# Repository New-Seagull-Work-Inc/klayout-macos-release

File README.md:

> **Binary release** — prebuilt `klayout` and `kplace`
> executables for macOS on Apple Silicon (arm64).
> Links against the system libSystem only; no other dependencies.
> Other platforms and distributions: build from the source
> repository when authorized by Seagull Work, Inc.
> **This package contains executables, one example
> KiCad board and the fab library — no source code is
> included or implied.**
> The `klayout` and `kplace` binaries, this README, the
> `LICENSE`, the `example/` board they route and the `fab/`
> folder (the fabs' published capabilities and stackups,
> JSON) are the entire distribution: there is no source tree, no
> Makefile, and nothing here that can be compiled,
> rebuilt, or modified. The example is design input for
> the tool, not program source.
> Nothing to build here: route the included board with
> `./klayout --input-dir example --output-dir out --resize-pcb`.
> Keep both binaries in the same directory: klayout invokes
> kplace for auto-placement and re-invokes itself for parallel
> attempts (install on PATH or run from their directory).
> kicad-cli from KiCad 10, found via PATH or KICAD_CLI,
> enables the DRC acceptance gates, zone-fill verification
> for the pour stitching, and the fab exports (gerbers,
> drill, pick-and-place, IPC-D-356).
> The `fab/` folder is the fab library the impedance model and the
> fab targeting read; it is described below.
> **Trial software, no warranty** — free to evaluate, and
> the layouts it produces are yours to use for anything,
> commercially included. Nothing it outputs is guaranteed
> or has been reviewed by an engineer: a clean DRC report
> is this program grading its own work, not an assurance
> that a board is manufacturable or safe. Verify every
> layout before you build it. Full terms in `LICENSE`.
> The build instructions carried by the source repository are
> omitted from this README: there is nothing here to compile.

# klayout — automatic placement and routing for KiCad boards

**Trial software.** This package is provided for evaluation under the
terms of the `LICENSE` file beside it. Read it before you use the
program; the layouts it produces are yours, the program is not.

## What it does

`klayout` takes a KiCad project — schematic, unrouted board, footprints —
and delivers a placed and routed board:

- **Places** the parts (`kplace`, invoked automatically) the way an
  experienced layout engineer would, from the board alone: every chip
  gets its decoupling and its two-pad satellites in rows along the
  edge that carries their pins; chips cluster into functional blocks
  (a regulator and its parts, a charger and its parts) ordered from
  the input connector; a connector's circuit sits at the connector,
  with the USB pair short and straight from the jack. Boards of four
  copper layers and up are placed on both faces from the first
  trial; two-layer boards start single-sided and go to both faces
  only when no single-sided trial routes every net.
  `--group-labeling` frames and names each block on the silkscreen
  (`Battery charger (U3)`, `Boost converter (U10)`).
- **Routes** every net on the layer count you ask for, through vias,
  with copper pours for the ground and power planes it reserves, and
  power rails at their IPC-2221 ampacity width.
- **Signal integrity built in.** Differential pairs are detected from
  the net names and routed as coupled pairs to their standard's
  impedance and skew budget (USB, PCIe, MIPI CSI/DSI, LVDS, Ethernet).
  DDR interfaces (DDR4, LPDDR4) are detected the same way: each byte
  lane is routed as a bundle on one inner layer with its strobe pair,
  length-matched to the strobe, at the standard's single-ended and
  differential impedance on the fab's real stackup.
- **Judges the signal integrity like a reviewer would.** DDR groups are
  gated on two tiers — the standard's spec (what training absorbs) and
  a shipped-quality target — and their impedance is judged against the
  DRAM's *legal* termination bins (LPDDR4 ODT 40/48/60/80/120/240 Ω) so
  the report names the firmware setting the copper needs. Home layers
  are ranked by the impedance they can actually carry on the fab's
  stackup (a 6-layer board's DDR lands on the outer layers, as the
  reference SoMs do). The **SI sign-off page** (below) adds eye
  diagrams, per-net openings, a timing budget and via-stub analysis.
- **Checks its own work.** Every board goes through KiCad's own DRC
  and ERC (`kicad-cli`); the verdict is `clean` only at zero errors,
  zero warnings, zero unconnected items, zero schematic-parity findings.
- **Tries several placements in parallel** and keeps the one that
  meets every gate, printing a table of the trials so you can see why.
- **Shows you the work as it happens** — the PCB Layout Cinema, a live
  view in your browser (below).
- **Builds to your fab's floors.** `--fab NAME` raises every design
  rule below the house's published minimums for the board's layer
  count, writes its stackup into the board, and judges the input at
  those floors too, so a footprint the house cannot etch is named as
  the input's problem, not the router's.
- **Delivers the fabrication package**: gerbers, drill files and maps,
  IPC-D-356 netlist, a sourced BOM, pick-and-place, fab drawings, a
  board render, the schematic as PDF, a copy of the design and a
  SHA-256 manifest, unless you ask it not to.
- **Keeps the console quiet.** A run prints one status line per
  trial (placing, routing pass, rip-up round, DRC, done) and the
  verdict; everything else goes to `klayout.log`.

## Quick start

```
./klayout --input-dir my-board --output-dir my-board-routed --layers 4
```

- `--input-dir` — a folder holding the KiCad project: the `.kicad_pcb`
  (parts may be unplaced; the design rules come from its `.kicad_pro`),
  the `.kicad_sch`, and the footprint / symbol libraries it uses.
- `--output-dir` — where the routed project is written. It is created.
- `--layers` — copper layers to route on (2, 4, 6, 8, 10, 12 …; `1`
  for a single-sided board with no vias).

Keep `klayout` and `kplace` in the same directory: `klayout` runs
`kplace` for placement and re-runs itself for the parallel attempts.

### What you get

Everything a run produces lives in the output directory:

```
my-board-routed/
  <board>.kicad_pcb            the placed and routed board: opens in KiCad,
                               pours filled, the fab's stackup written in,
                               designators straightened and kept off silk
  <board>.kicad_pro, .kicad_prl, .kicad_sch, fp-lib-table, sym-lib-table,
  <libs>.pretty/, <libs>.kicad_sym
                               the rest of the project, copied beside the
                               board so it opens as a whole; the project's
                               DRC minimums raised to the fab's floors
  <board>-klayout-result.json  the verdict (below)
  klayout.log                  everything the run did: the trial table,
                               placement and routing passes, the impedance,
                               skew and reflection reports, DRC and ERC
  placement-report.txt         boards that were placed: wirelength before
                               and after, the pin pulls, each part's move
                               (beside the board, or in the kept trial's
                               folder when that trial placed it)
  si-report/                   boards built on a fab's stackup: the copper
                               as laid, per net — segments.csv, vias.csv,
                               pads.csv — the reflection data an SI review
                               starts from, and si-report.pdf built on it
                               (reflections per DDR net; per serial lane its
                               eye at the receiver and its impedance along
                               the lane)
  fabrication/                 the manufacturing package (below);
                               --gerber-dir moves it, --no-fab skips it
  .input/                      a read-only copy of the input, judged by the
                               same DRC at the fab's floors, so the verdict
                               can separate the board's own violations from
                               anything the router introduced
  .att0/ … .att7/, .att0.log … the placement trials, each a full project
                               with that trial's board and log (hidden
                               dot-files; `ls -a`)
  <board>.progress.json        the frame the PCB Layout Cinema is drawing
  <board>.progress.jsonl       every frame of that trial, one per line (each
                               holds what changed since the frame before), so
                               the Cinema plays the run back after it ends
```

The fabrication package, in the layout a board house and an assembler
both expect:

```
fabrication/
  gerbers/            <board>-<Layer>.gbr for every copper, mask, silk and
                      paste layer plus the outline, and <board>-job.gbrjob
    drill/            <board>-PTH.drl, <board>-NPTH.drl (Excellon, mm), a
                      PDF drill map per file, drill-report.rpt
  electrical-test/    <board>.d356 — the IPC-D-356 netlist for bare-board test
  assembly/           <board>-bom.csv — one row per reference: Reference,
                      Value, Footprint, Quantity, Manufacturer, MPN,
                      Datasheet, Lifecycle, Supplier, SKU, Product URL,
                      Available, Verified On, Unit Price, DNP
                      <board>-positions.csv — pick-and-place, both sides,
                      mm, populated parts only
                      for a JLCPCB board also <board>-bom-jlcpcb.csv —
                      Comment, Designator, Footprint, LCSC (from each
                      part record; blank where it has none) — and
                      <board>-positions-jlcpcb.csv — Designator, Mid X,
                      Mid Y, Layer, Rotation (rotations as KiCad
                      exports them: check bottom parts in JLCPCB's
                      placement preview)
                      drawings-svg/ — front and back fab drawings
  documentation/      <board>-board-render.png (top view),
                      schematic/<board>.pdf, si-report.pdf (a copy of
                      si-report/si-report.pdf), pdn-impedance.html and
                      .csv (the rail impedance curves, when the board
                      declares rails)
  design/             the board, project, schematic, tables and libraries
                      as sent to manufacture
  manifest.json       every file with its size and SHA-256, the source
                      board's hash, the kicad-cli version, the run's DRC counts
```

The BOM's sourcing columns come from the footprint's own fields
(Manufacturer, MPN, Datasheet) when the schematic carries them, and
otherwise from the parts library (below). The library holds each
part's design record, and the BOM takes from it the manufacturer, the
part number, the datasheet when the record names one, and, where the
record carries them, the distributor, the stock and the lowest-volume
price (a bare number: the record states no currency). Lifecycle, SKU,
product link and verification date are not in a design record and stay
empty. A part with no record keeps its row with those columns empty, so
the BOM always lists every part on the board.

### The PCB Layout Cinema

Every run serves a live view of the routing and opens it in your default
browser (Safari, Chrome and Firefox all work):

```
http://localhost:8765/
```

One panel per placement trial, drawn as it routes — the copper laid
since the last frame in white — with completion bars per signal class
(differential pairs and DDR, other signals, power), the current stage,
the elapsed time, and a scrub bar over the run's frames. **Step frame by
frame** with the ‹ › buttons beside the bar, or click a panel and use
the ← → keys (space returns to live); the counter shows which frame you
are on. Every frame is kept on disk in each trial's
<board>.progress.jsonl, so a reloaded page, or `--watch` on a finished
run or on its archived copy, steps through all of them. The run ends on two frames: what the last pass laid, highlighted
white, then the finished board in its layer colours.
Once a trial is kept the title reads **writing outputs** while the
run writes the board, the fabrication package and the reports -- the
clock runs on -- and **ended** when the run is done.
If the page does not open by itself, open that address (or
`http://127.0.0.1:8765/`) while the run is going. To watch a finished
run again:

```
./klayout --watch my-board-routed
```

`KLAYOUT_NO_BROWSER=1` keeps the browser closed (the server still runs),
`KLAYOUT_DASH_PORT=NNNN` picks another port, `KLAYOUT_NO_DASH=1` turns
the Cinema off.

## Other options

All options are `klayout --help`. The ones you are likely to use:

| option | meaning |
|---|---|
| `--plane NET:LAYER` | pour a copper zone for that net on that layer (`--plane GND:In2.Cu`); repeatable. Without it the tool reserves ground and power layers itself from the layer count. |
| `--stack SPEC` | the stackup by role, outermost first, e.g. `SIG-GND-SIG-GND-PWR:3V3-SIG`; sets `--layers` and the planes at once. |
| `--place-tries N` | placement trials in the first wave (default: as many as the machine has performance and super cores, all at once). A trial that ends without a clean board hands its slot to a new trial with a new placement, until one is clean. The first **clean** trial -- every gate met, and no DRC error, DRC warning or unconnected item added over the input -- stops the others and is kept. Each trial's line in the log names what it left unconnected (`trial 3/6 left unconnected: NET: Pad 2 of C12 -- Track ... at (x, y)`). |
| `--seed N` | base placement seed (default 1) — same command, same board, same result. |
| `--resize-pcb` | after routing, shrink the outline to the smallest DRC-legal rectangle around the design. |
| `--grid`, `--track`, `--clearance`, `--via-size`, `--via-drill`, `--edge-clearance`, `--hole-clearance` (mm) | override the design rules read from the `.kicad_pro`. |
| `--fab NAME` | the board house you will use: its floors become the minimum for every rule and its stackup is written into the board (see the fab library below). |
| `--fab-dir DIR` | where the fab library is (default: `fab/` beside the binaries; `KLAYOUT_FAB_DIR` does the same; `none` runs without it). |
| `--group-labeling` | frame and name the functional blocks on the front silkscreen; off, the blocks pack as tightly as the rows allow and nothing is drawn. |
| `--no-fab` | skip the fabrication package. |
| `--gerber-dir DIR` | write the fabrication package somewhere else. |
| `--split-ps` | split a board larger than a power supply into `<base>-PS` (the mains sheet) and `<base>-MB` (everything else) and route the two separately. |
| `--si-layer-min F` | the share of a DDR lane member's copper that must stay on its home layer (default 0.90); `--si-any-layer` lifts the home-layer rule altogether. |
| `--eight-angles-routing` | 90°/45° turns only, no any-angle shortcuts. Every board is tried this way first; only a board that ends below its gates is retried any-angle, and a DDR board that is complete and DRC-clean stays octilinear. |
| `--arc-wiggles`, `--sine-wiggles` | the shape of length-matching meanders: arc accordions or sinusoids instead of rectangular bumps. |
| `--no-widen` | ignore `power.json`: route power rails at the class width instead of their IPC-2221 ampacity width. |
| `--watch DIR` | serve the PCB Layout Cinema for a finished run. |
| `--version` | print the build revision. |

Environment: `KICAD_CLI=/path/to/kicad-cli` if it is not on your PATH;
`KLAYOUT_OFFLINE=1` to keep the tool from touching the network;
`KLAYOUT_NO_SWEEP=1` to skip the fab sweep (below) when a board ends
below its gates.

## The parts library

The parts library ships beside the executables as `parts/`: the fab library and the parts the
examples use. klayout reads it from there; nothing else is needed.

## The fab library — the `fab/` folder

Four JSON files, one per board house — `jlcpcb.json`, `osh_park.json`,
`advanced_circuits.json`, `sierra_circuits.json` — holding what each
house **publishes** on its capability and impedance pages:

- the manufacturing floors: minimum track width and spacing, drill,
  via diameter and annular ring, hole-to-hole and board-edge
  clearances, layer counts, board thicknesses, copper weights,
  materials, finishes;
- where the house publishes them, its **impedance-controlled stackups**
  (`"stackups"`): for each layer count the stack from top to bottom —
  copper foils with their weight, cores and prepregs with their
  thickness, material and dielectric constant;
- `source_url` and `retrieved_utc`, so every number can be checked
  against the house's page.

klayout uses the folder three ways:

1. **Target fab** — `--fab NAME` (or a `(fab "NAME")` clause in the
   design file) raises any project rule below that house's floor and
   writes its stackup into the board.
2. **Impedance** — every differential pair and every DDR lane member is
   solved on the declared house's stackup for the board's layer count
   (with none declared, the first house that publishes one; the log
   names it): the microstrip model on the outer layers, the stripline
   model between the planes on the inner ones. The report then measures
   the copper **as laid** — `impedance: target 80 ohm, as laid ~82 ohm,
   91% of the copper within 10%` — rather than restating the solve.
3. **Fab sweep** — when a board ends below its gates, it is re-routed
   under each house's floors and the report names the houses that could
   build it.

Without the folder the tool still routes, but the impedance model falls
back to an assumed stackup and DDR lanes keep the class width; the log
says so. To add a house, drop a JSON file in the same shape as the
others, with the numbers from its public pages and the `source_url`
kept.

## Reading the result

The log ends with the verdict. For a board with differential pairs or
DDR, the **trial table** comes first — one row per placement trial,
a check or a cross in every gate cell:

```
┌───────┬──────┬────────┬──────────┬───────────┬────────────────┬──────────────────┬──────────────────┬─────────────────┬─────────────────────┬─────────────────────┬────────────────────┐
│ trial │ time │ gates  │ unrouted │ DRC e/w/u │ pair skew mm   │ DQS0 lane skew   │ DQS1 lane skew   │ ADDR/CK skew    │ home layer          │ pairs Z as laid     │ DQS0 lane Z        │
├───────┼──────┼────────┼──────────┼───────────┼────────────────┼──────────────────┼──────────────────┼─────────────────┼─────────────────────┼─────────────────────┼────────────────────┤
│ 1     │ 8:48 │ met ✓  │ 0 ✓      │ 0/0/0 ✓   │ 0.007 / 2.55 ✓ │ 0.174 / 2.05 ✓   │ 0.052 / 2.05 ✓   │ 3.091 / 16.00 ✓ │ 0 miss, worst 93% ✓ │ 81-84 ohm, 91% in ✓ │ 44.1 ohm, 72% in ✗ │
└───────┴──────┴────────┴──────────┴───────────┴────────────────┴──────────────────┴──────────────────┴─────────────────┴─────────────────────┴─────────────────────┴────────────────────┘
```

Skew cells show the worst member against its budget; "home layer" the
lane members below the required share and the worst one's share;
impedance cells the length-weighted impedance of the copper as laid and
how much of it is within 10 % of the target (the check when the mean is
within 10 %). Then:

- `clean: true` in the result file — DRC 0 errors / 0 warnings / 0
  unconnected, schematic parity 0, ERC 0/0, no routing failures. A board
  that routes but is not clean is still written, with `*** NOT CLEAN`
  and the counts in the log. The result file also carries `fab_target`
  (the house whose floors the board was built to), `gates_met`,
  `si_pairs_missed`, `stitch_bonds`, the `placement_constraints` read
  from the design file and any violations, and `outputs` — the path of
  the fabrication package and of each of its parts.
- **Violations that were already on the input board** are named as such:
  the tool runs the same DRC on the input (read-only) and the final
  message says how many of the reported errors and warnings were there
  before routing and how many the router introduced — and, when nothing
  beyond the input's own findings remains, says so. The result file
  carries `input_drc`, `introduced` and `clean_beyond_input`. A pad
  overlapping its own footprint's hole, a library footprint mismatch,
  an unplaced part's courtyard: those are the board's to fix, not the
  router's.
- The per-pair and per-lane reports above the table: skew, home-layer
  share, impedance as laid, via counts.

KiCad's own DRC is the ground truth; open the board in KiCad or run
`kicad-cli pcb drc` on it yourself to confirm.

## The SI report

Every run on a fab's stackup ends with `si-report.pdf` (in `si-report/`
beside its CSVs, and a copy in the fabrication package's
`documentation/`), written by klayout itself. Page one states the model,
every parameter and its source (the standard, the parts' datasheets).

- **DDR nets** — each net chained driver to receiver through the copper
  as laid, every run a transmission line at its own as-laid impedance,
  simulated exactly (lossless, reflections only). Per group (DQ / CA) the
  legal LPDDR4 drive strength and ODT that clears the most nets is chosen;
  each net is judged on overshoot and ringback, with a page showing its
  impedance along the path and the edge at the receiver.
- **Serial links** — a pair whose ends are a known transmitter and
  receiver (a MIPI CSI-2 D-PHY sensor into a serializer or SoC; a TI
  V3Link forward channel) is judged by that link's own standard: the
  worst-case eye at the receiver at the parts' data rate and limits,
  against the receiver's threshold window, beside the lane's differential
  impedance along its length, its return loss and its S-parameters
  (SDD11, SDD21) to the fifth harmonic.

To draw it again for an output directory: `./klayout --si-report OUTPUT_DIR
[PDF]`.

The console lane table (per pair: home layer, skew against budget,
differential impedance as laid, share of the copper within 10 % of the
target) and the rail impedance curves (`pdn-impedance.html` and `.csv`)
come with every run too, and so do the two sign-off pages,
`signoff-si.html` and `signoff-pi.html` (each with its PDF): the verdict,
the results against every gate, the eye diagrams, the conditions for
sign-off, and the rails against their ampacity and IR-drop budgets. To
write them again for routed output directories: `./klayout --signoff DIR
[DIR ...] [-o OUT_DIR] [--label BUILD]`.

## Requirements

- The platform named at the top of this file.
- **KiCad 10** with `kicad-cli` on your PATH (or `KICAD_CLI` set). Without
  it the board still routes, but the DRC / ERC gates, the pour
  verification and the fab package are skipped, and the verdict says so.
- Both binaries in the same directory.
- Nothing else: no Python, no other runtime or package. `klayout` and
  `kplace` are self-contained C programs; every report (SI report, sign-off
  pages, regulator report, their PDFs) is written by `klayout` itself.
- On macOS, if Gatekeeper blocks the downloaded binaries, clear the
  quarantine flag once: `xattr -d com.apple.quarantine klayout kplace`.

## Limitations

- Through vias only — no blind, buried or micro vias.
- Copper already in the input board is left as it is: a pre-routed pair
  is frozen and reported, not completed.
- One track width and clearance for ordinary nets; pairs, DDR lane
  members and power rails get their own solved widths.
- Trapezoid and custom pad shapes are treated as their bounding circle.
- A differential pair needs equal P and N pad counts (2–8 per member).
- Zones present in the input board are not treated as obstacles; the
  pours klayout emits are.

## License

See `LICENSE`. This is a trial: free to evaluate, no warranty, and
nothing the program outputs has been reviewed by an engineer — a clean
DRC report is the program grading its own work. Verify every layout
before you build it.

## Examples in this package

Each example lays out from this package as shown; the release gate ran each one this way and it met
every gate (KiCad DRC, unconnected, parity and ERC at zero; the electrical checks it states).

### can-node

A CAN bus node on four layers: placement from scratch, and the CAN differential pair routed to its impedance.

- Parts: MCP2515 CAN controller with 8 MHz crystal, SN65HVD230 transceiver, split termination behind a jumper, NUP2105L bus protection, screw terminal, reverse-polarity diode, NCP1117-3.3 regulator, power LED, host header. 23 parts, 27 nets.
- Board: 56 x 36 mm, 4 copper layers, JLCPCB's published 4-layer stackup.
- What the layout tool does: places every part (they start beside the board), routes it, and routes CANH / CANL as a 100 ohm pair.
- Built only from KiCad's standard symbol and footprint libraries.
- Not judged: the supply rails (this board states no rail voltages or currents).

Run it from the package folder:

    ./klayout --input-dir example/can-node --output-dir out/can-node --layers 4 --fab jlcpcb

### usb-mcu

A USB full-speed microcontroller board on four layers: placement from scratch, and a USB 2.0 differential pair routed to its impedance and skew budget.

- Parts: USB-C receptacle, USBLC6-2SC6 ESD protection, STM32F042K6T6 microcontroller, AP2112K-3.3 regulator, 8 MHz crystal, reset and boot buttons, SWD header, two LEDs, two GPIO headers. 28 parts, 38 nets.
- Board: 60 x 40 mm, 4 copper layers, JLCPCB's published 4-layer stackup.
- What the layout tool does: places every part (they start beside the board), routes it, and routes USB D+ / D- as a pair through the ESD part to the microcontroller, held to 90 ohm +-15 % and a 1.27 mm length match.
- Built only from KiCad's standard symbol and footprint libraries.
- Not judged: the supply rails (this board states no rail voltages or currents).

Run it from the package folder:

    ./klayout --input-dir example/usb-mcu --output-dir out/usb-mcu --layers 4 --fab jlcpcb

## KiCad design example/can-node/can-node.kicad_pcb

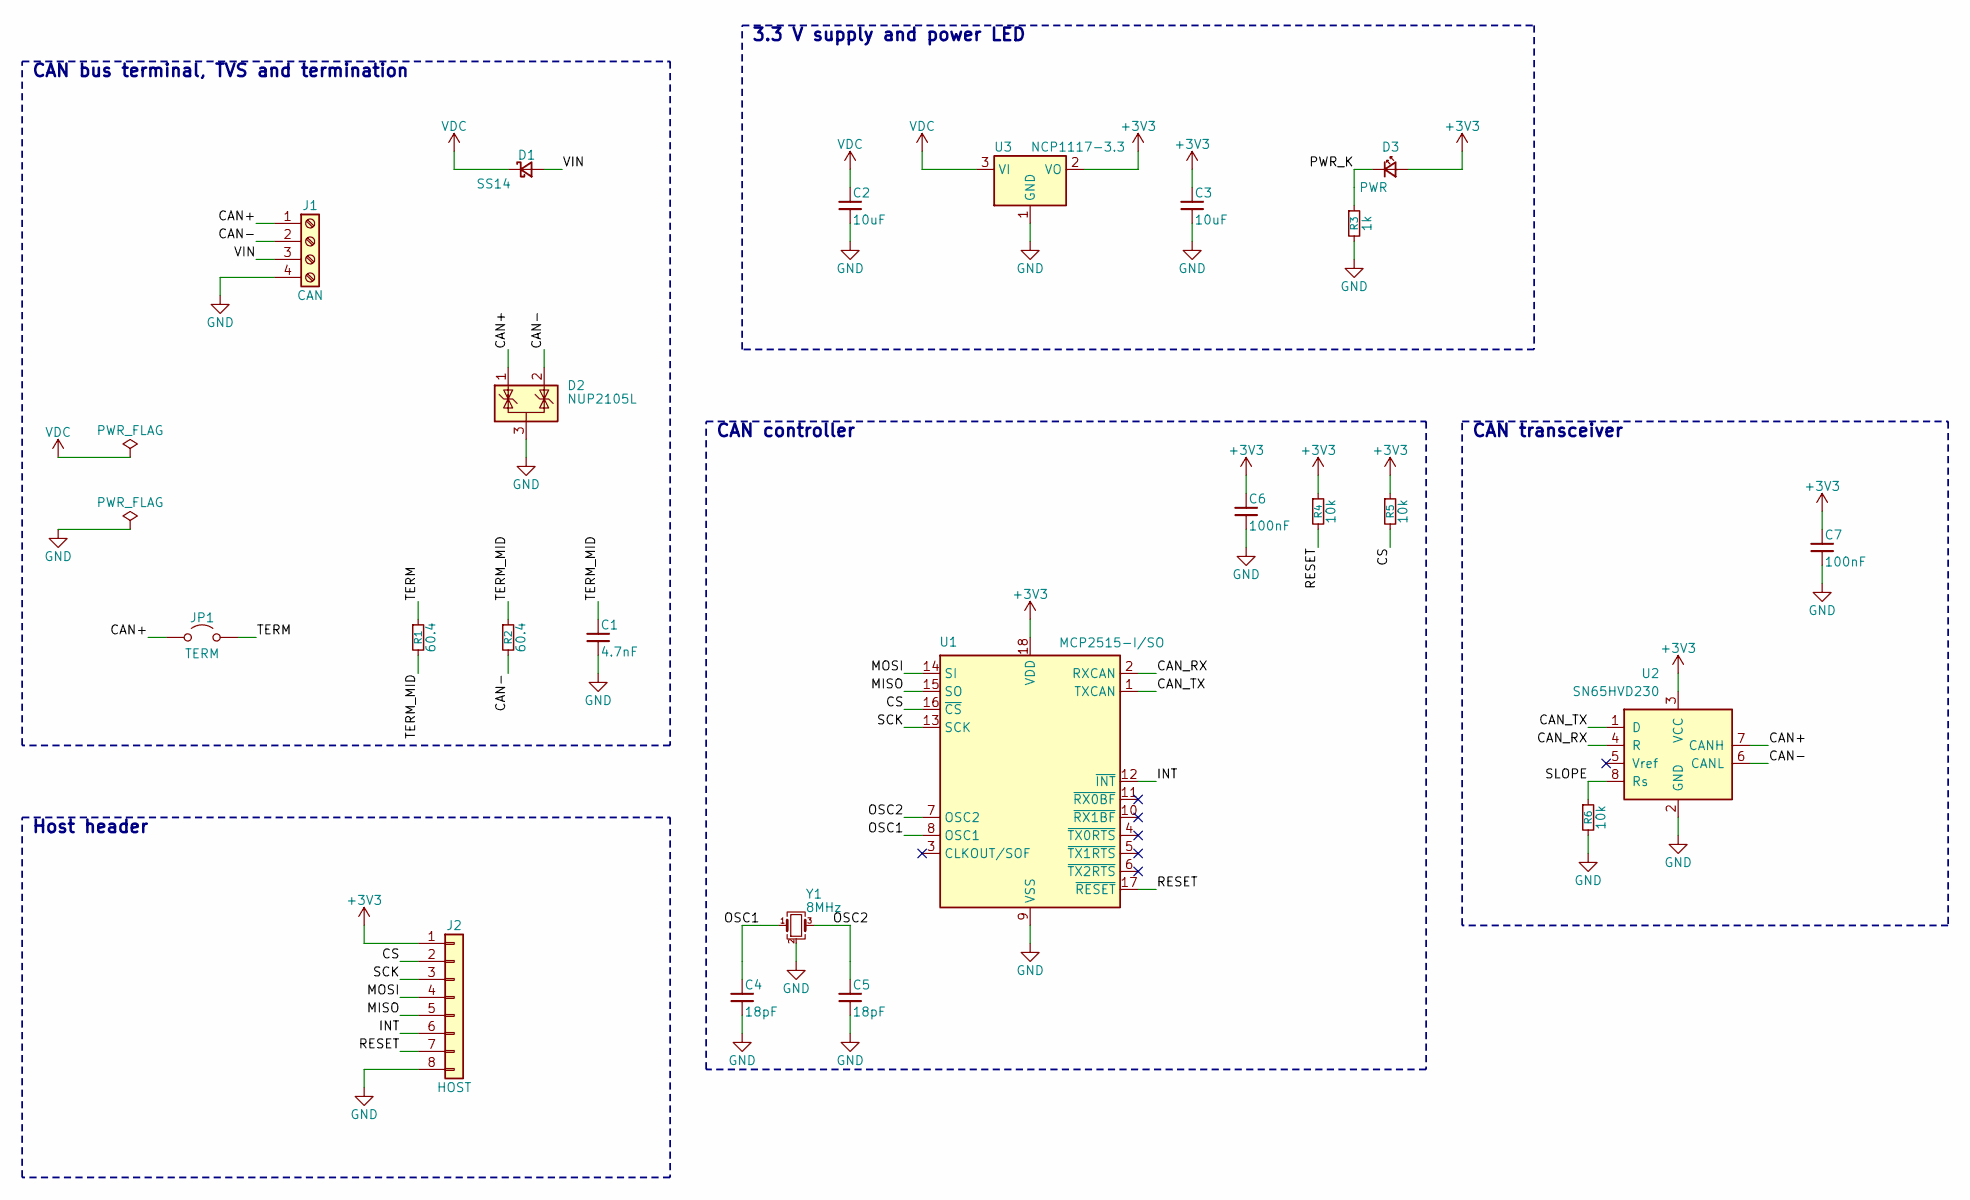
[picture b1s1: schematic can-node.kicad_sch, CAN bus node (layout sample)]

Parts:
C1: 4.7nF; C_0603_1608Metric
C2, C3: 10uF; C_0805_2012Metric
C4, C5: 18pF; C_0603_1608Metric
C6, C7: 100nF; C_0603_1608Metric
D1: SS14; D_SMA
D2: NUP2105L; SOT-23
D3: PWR; LED_0603_1608Metric
J1: CAN; TerminalBlock_Phoenix_PT-1,5-4-3.5-H_1x04_P3.50mm_Horizontal
J2: HOST; PinHeader_1x08_P2.54mm_Vertical
JP1: TERM; PinHeader_1x02_P2.54mm_Vertical
R1, R2: 60.4; R_0805_2012Metric
R3: 1k; R_0603_1608Metric
R4, R5, R6: 10k; R_0603_1608Metric
U1: MCP2515-I/SO; SOIC-18W_7.5x11.6mm_P1.27mm
U2: SN65HVD230; SOIC-8_3.9x4.9mm_P1.27mm
U3: NCP1117-3.3; SOT-223-3_TabPin2
Y1: 8MHz; Crystal_SMD_3225-4Pin_3.2x2.5mm

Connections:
+3V3: C3.1, C6.1, C7.1, D3.2 (A), J2.1, R4.1, R5.1, U1.18 (VDD), U2.3 (VCC), U3.2 (VO)
/CAN+: D2.1 (K), J1.1, JP1.1 (A), U2.7 (CANH)
/CAN-: D2.2 (K), J1.2, R2.2, U2.6 (CANL)
/CAN_RX: U1.2 (RXCAN), U2.4 (R)
/CAN_TX: U1.1 (TXCAN), U2.1 (D)
/CS: J2.2, R5.2, U1.16 (~CS)
/INT: J2.6, U1.12 (~INT)
/MISO: J2.5, U1.15 (SO)
/MOSI: J2.4, U1.14 (SI)
/OSC1: C4.1, U1.8 (OSC1), Y1.1
/OSC2: C5.1, U1.7 (OSC2), Y1.3
/PWR_K: D3.1 (K), R3.1
/RESET: J2.7, R4.2, U1.17 (~RESET)
/SCK: J2.3, U1.13 (SCK)
/SLOPE: R6.1, U2.8 (Rs)
/TERM: JP1.2 (B), R1.1
/TERM_MID: C1.1, R1.2, R2.1
/VIN: D1.2 (A), J1.3
GND: C1.2, C2.2, C3.2, C4.2, C5.2, C6.2, C7.2, D2.3 (A), J1.4, J2.8, R3.2, R6.2, U1.9 (VSS), U2.2 (GND), U3.1 (GND), Y1.2 (G), Y1.4 (G)
VDC: C2.1, D1.1 (K), U3.3 (VI)

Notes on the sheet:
CAN controller
Host header
3.3 V supply and power LED
CAN bus terminal, TVS and termination
CAN transceiver

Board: 2 copper layers, 23 parts (0 on the bottom side), 20 nets, no tracks yet.

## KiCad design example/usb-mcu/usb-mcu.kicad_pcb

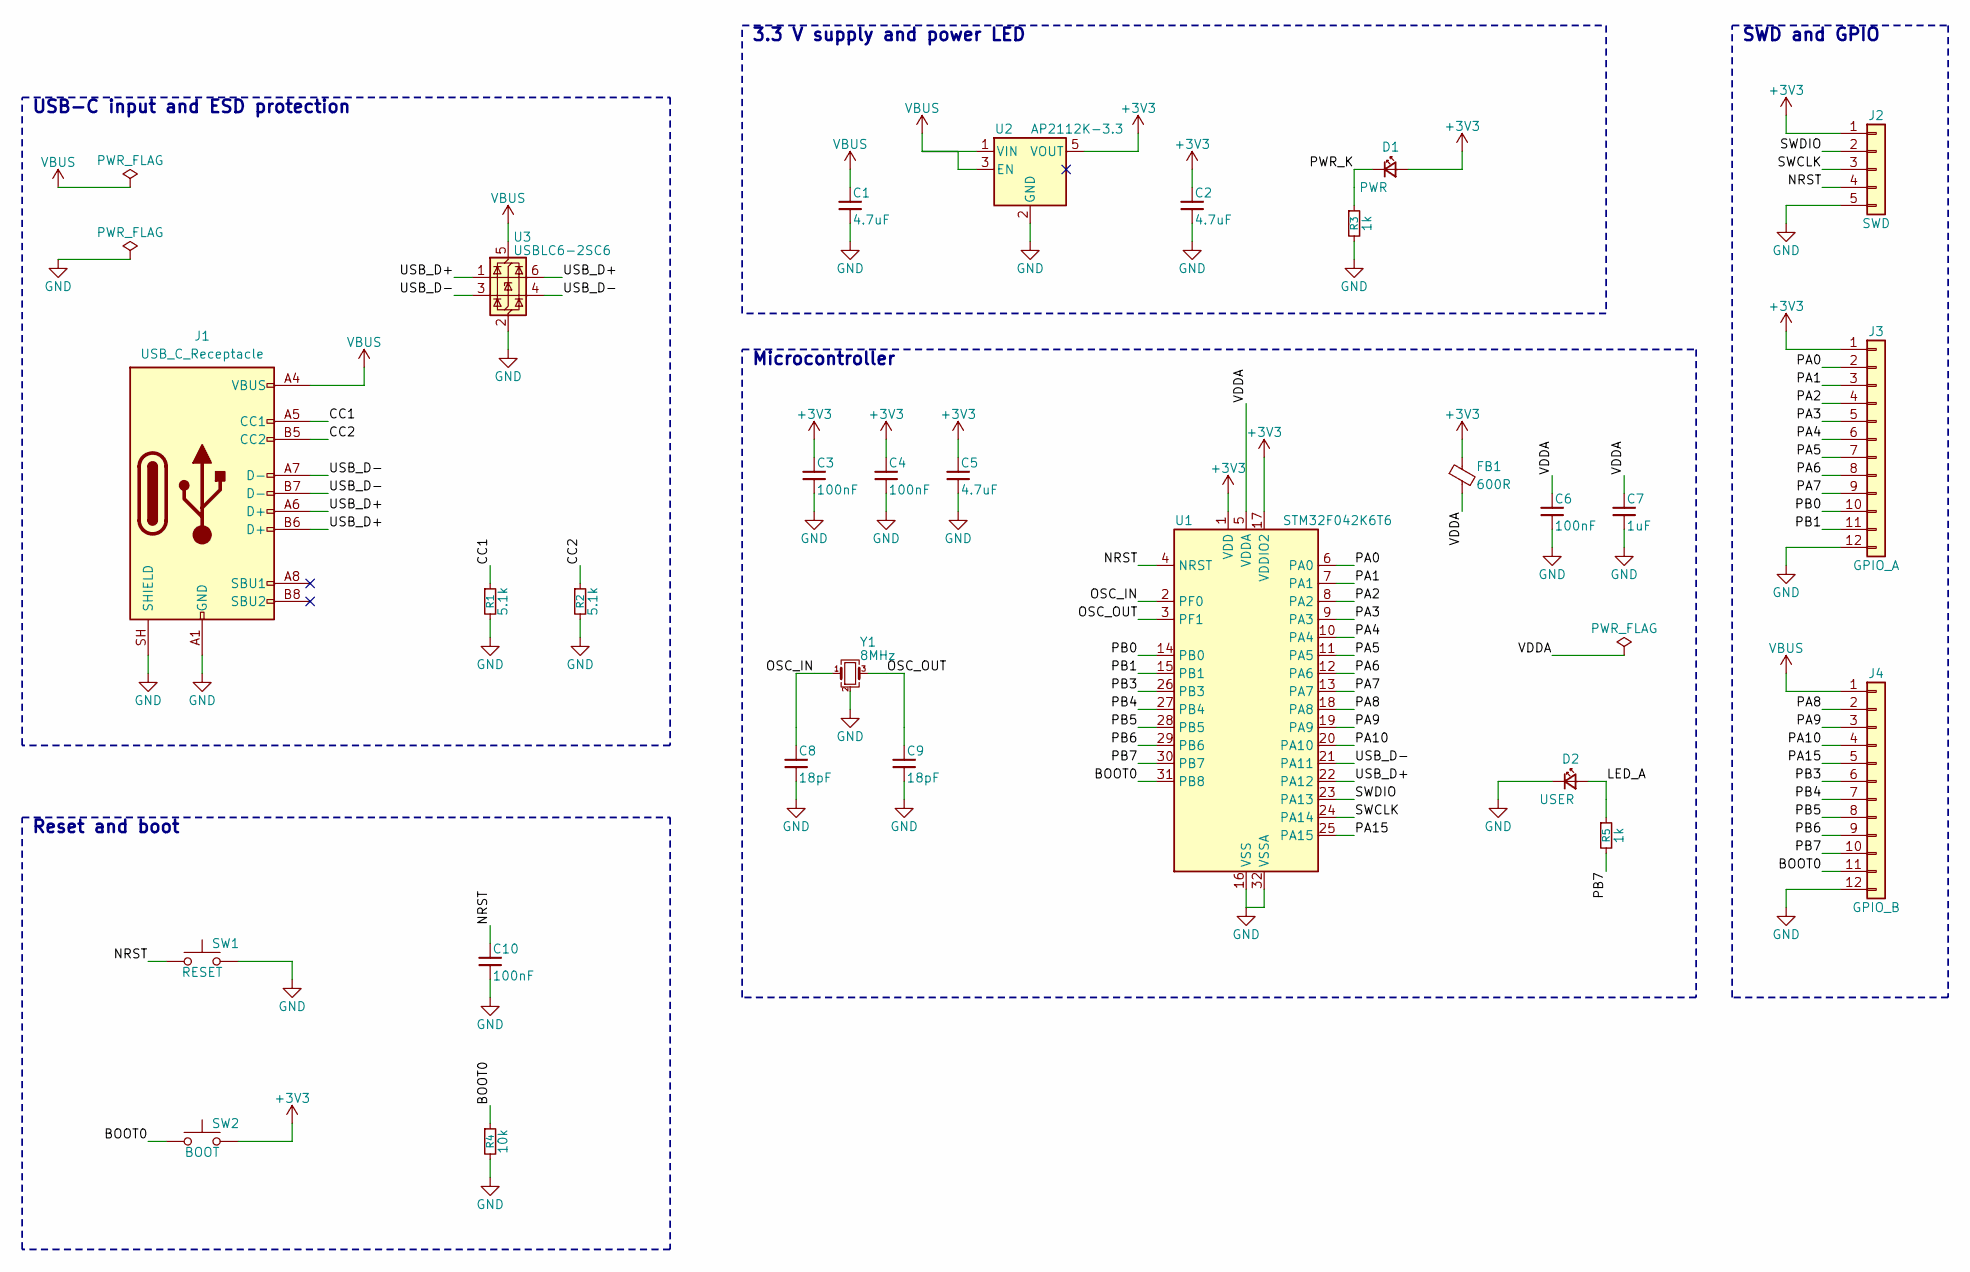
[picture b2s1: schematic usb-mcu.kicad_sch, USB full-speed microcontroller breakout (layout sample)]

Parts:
C1, C2: 4.7uF; C_0805_2012Metric
C3, C4, C6, C10: 100nF; C_0603_1608Metric
C5: 4.7uF; C_0603_1608Metric
C7: 1uF; C_0603_1608Metric
C8, C9: 18pF; C_0603_1608Metric
D1: PWR; LED_0603_1608Metric
D2: USER; LED_0603_1608Metric
FB1: 600R; L_0603_1608Metric
J1: USB_C_Receptacle; USB_C_Receptacle_HRO_TYPE-C-31-M-12
J2: SWD; PinHeader_1x05_P2.54mm_Vertical
J3: GPIO_A; PinHeader_1x12_P2.54mm_Vertical
J4: GPIO_B; PinHeader_1x12_P2.54mm_Vertical
R1, R2: 5.1k; R_0603_1608Metric
R3, R5: 1k; R_0603_1608Metric
R4: 10k; R_0603_1608Metric
SW1: RESET; SW_SPST_B3U-1000P
SW2: BOOT; SW_SPST_B3U-1000P
U1: STM32F042K6T6; LQFP-32_7x7mm_P0.8mm
U2: AP2112K-3.3; SOT-23-5
U3: USBLC6-2SC6; SOT-23-6
Y1: 8MHz; Crystal_SMD_3225-4Pin_3.2x2.5mm

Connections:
+3V3: C2.1, C3.1, C4.1, C5.1, D1.2 (A), FB1.1, J2.1, J3.1, SW2.2, U1.1 (VDD), U1.17 (VDDIO2), U2.5 (VOUT)
/BOOT0: J4.11, R4.1, SW2.1, U1.31 (PB8)
/CC1: J1.A5 (CC1), R1.1
/CC2: J1.B5 (CC2), R2.1
/LED_A: D2.2 (A), R5.1
/NRST: C10.1, J2.4, SW1.1, U1.4 (NRST)
/OSC_IN: C8.1, U1.2 (PF0), Y1.1
/OSC_OUT: C9.1, U1.3 (PF1), Y1.3
/PA0: J3.2, U1.6 (PA0)
/PA1: J3.3, U1.7 (PA1)
/PA2: J3.4, U1.8 (PA2)
/PA3: J3.5, U1.9 (PA3)
/PA4: J3.6, U1.10 (PA4)
/PA5: J3.7, U1.11 (PA5)
/PA6: J3.8, U1.12 (PA6)
/PA7: J3.9, U1.13 (PA7)
/PA8: J4.2, U1.18 (PA8)
/PA9: J4.3, U1.19 (PA9)
/PA10: J4.4, U1.20 (PA10)
/PA15: J4.5, U1.25 (PA15)
/PB0: J3.10, U1.14 (PB0)
/PB1: J3.11, U1.15 (PB1)
/PB3: J4.6, U1.26 (PB3)
/PB4: J4.7, U1.27 (PB4)
/PB5: J4.8, U1.28 (PB5)
/PB6: J4.9, U1.29 (PB6)
/PB7: J4.10, R5.2, U1.30 (PB7)
/PWR_K: D1.1 (K), R3.1
/SWCLK: J2.3, U1.24 (PA14)
/SWDIO: J2.2, U1.23 (PA13)
/USB_D+: J1.A6 (D+), J1.B6 (D+), U1.22 (PA12), U3.1 (I/O1), U3.6 (I/O1)
/USB_D-: J1.A7 (D-), J1.B7 (D-), U1.21 (PA11), U3.3 (I/O2), U3.4 (I/O2)
/VDDA: C6.1, C7.1, FB1.2, U1.5 (VDDA)
GND: C1.2, C2.2, C3.2, C4.2, C5.2, C6.2, C7.2, C8.2, C9.2, C10.2, D2.1 (K), J1.A1 (GND), J1.A12 (GND), J1.B1 (GND), J1.B12 (GND), J1.SH (SHIELD), J2.5, J3.12, J4.12, R1.2, R2.2, R3.2, R4.2, SW1.2, U1.16 (VSS), U1.32 (VSSA), U2.2 (GND), U3.2 (GND), Y1.2 (G), Y1.4 (G)
VBUS: C1.1, J1.A4 (VBUS), J1.A9 (VBUS), J1.B4 (VBUS), J1.B9 (VBUS), J4.1, U2.1 (VIN), U2.3 (EN), U3.5 (VBUS)

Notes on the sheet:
3.3 V supply and power LED
SWD and GPIO
Microcontroller
Reset and boot
USB-C input and ESD protection

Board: 2 copper layers, 28 parts (0 on the bottom side), 35 nets, no tracks yet.

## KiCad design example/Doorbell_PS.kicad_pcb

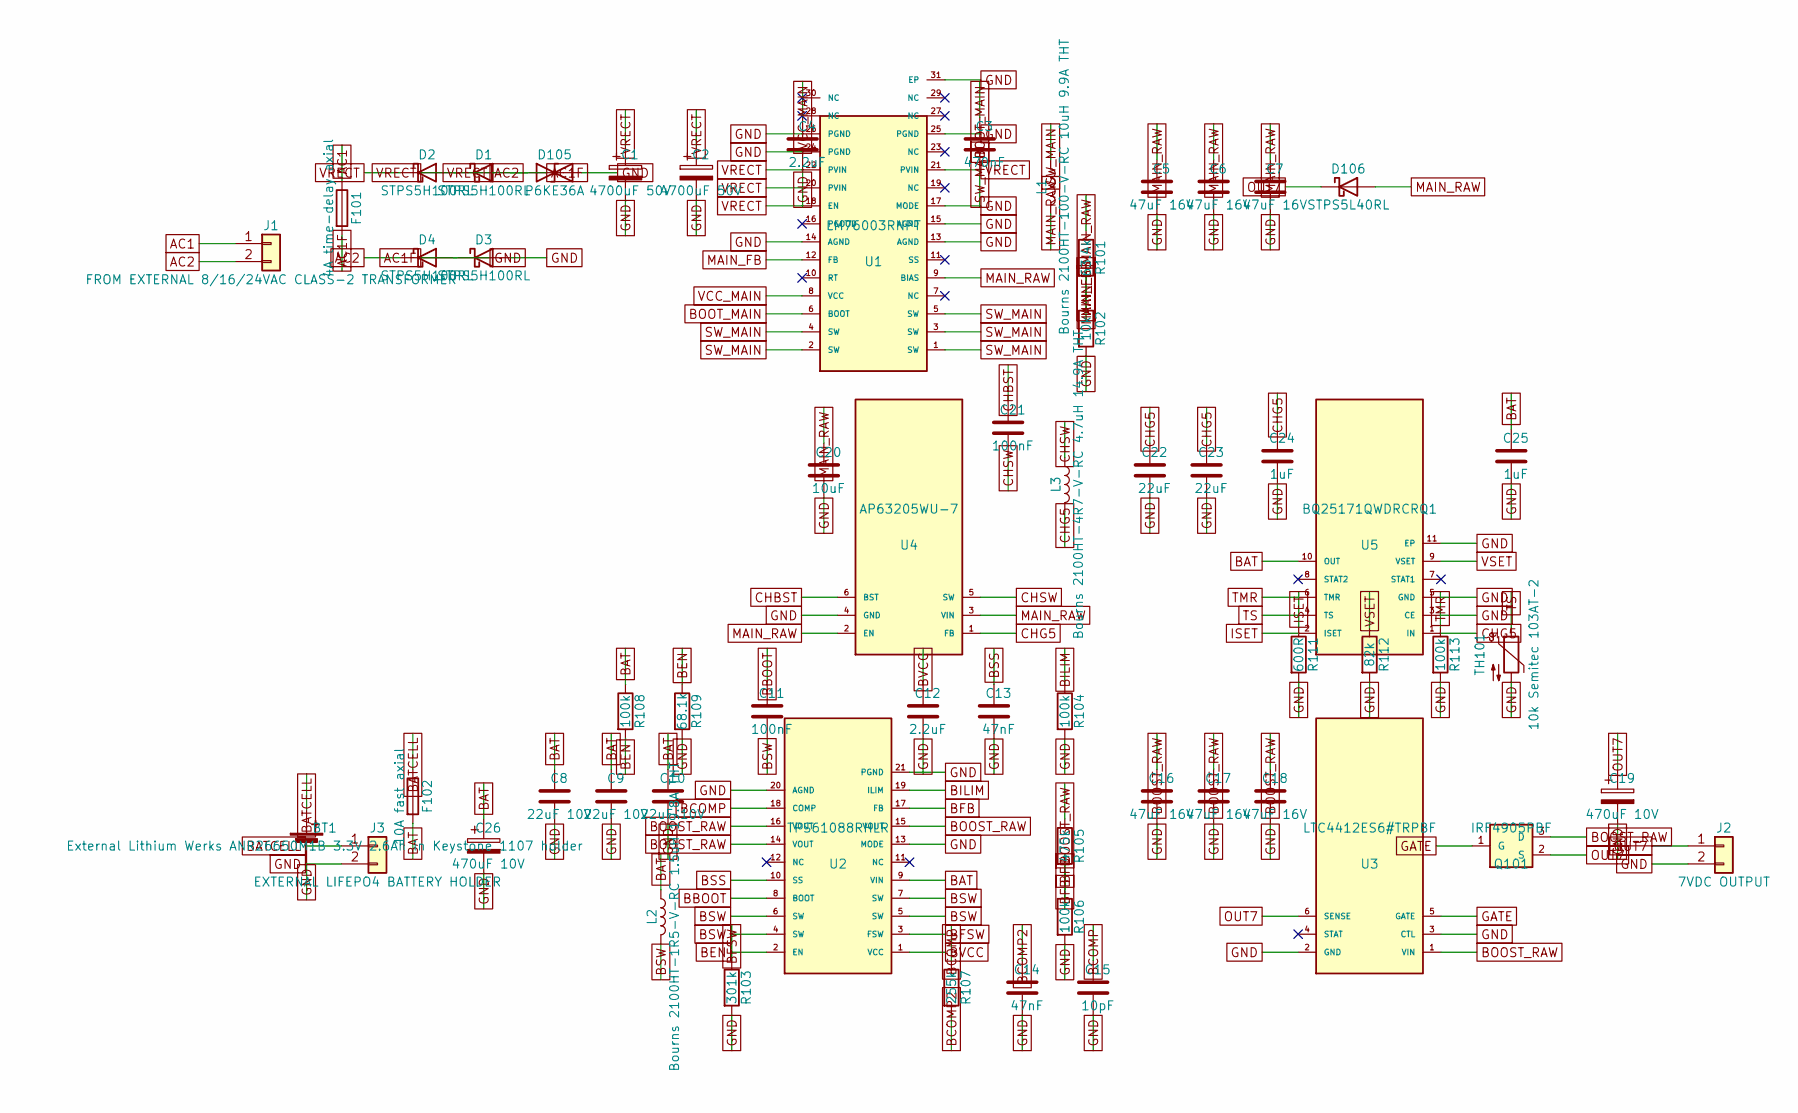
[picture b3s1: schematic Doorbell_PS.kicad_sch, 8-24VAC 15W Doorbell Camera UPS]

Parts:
BT1: External Lithium Werks ANR26650M1B 3.3V 2.6Ah in 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
C1, C2: 4700uF 50V; CP_Radial_D18.0mm_P7.50mm
C3: 470nF; C_0603_1608Metric
C4: 2.2uF; C_0603_1608Metric
C5, C6, C7, C16, C17, C18: 47uF 16V; C_1210_3225Metric
C8, C9, C10: 22uF 10V; C_1206_3216Metric
C11, C21: 100nF; C_0603_1608Metric
C12: 2.2uF; C_0805_2012Metric
C13, C14: 47nF; C_0603_1608Metric
C15: 10pF; C_0603_1608Metric
C19, C26: 470uF 10V; CP_Radial_D8.0mm_P3.50mm
C20: 10uF; C_1206_3216Metric
C22, C23: 22uF; C_1206_3216Metric
C24, C25: 1uF; C_0603_1608Metric
D1, D2, D3, D4: STPS5H100RL; D_DO-201AD_P15.24mm_Horizontal
D105: P6KE36A; D_DO-15_P10.16mm_Horizontal
D106: STPS5L40RL; D_DO-201AD_P15.24mm_Horizontal
F101: 4A time-delay axial; Fuse_Axial_P10.16mm
F102: 10A fast axial; Fuse_Axial_P10.16mm
J1: FROM EXTERNAL 8/16/24VAC CLASS-2 TRANSFORMER; TerminalBlock_Phoenix_MKDS-1,5-2_1x02_P5.00mm_Horizontal
J2: 7VDC OUTPUT; TerminalBlock_Phoenix_MKDS-1,5-2_1x02_P5.00mm_Horizontal
J3: EXTERNAL LIFEPO4 BATTERY HOLDER; TerminalBlock_Phoenix_MKDS-1,5-2_1x02_P5.00mm_Horizontal
L1: Bourns 2100HT-100-V-RC 10uH 9.9A THT; Bourns_2100HT_Vertical_P8.38mm
L2: Bourns 2100HT-1R5-V-RC 1.5uH 19.8A THT; Bourns_2100HT_Vertical_P8.38mm
L3: Bourns 2100HT-4R7-V-RC 4.7uH 14.9A THT; Bourns_2100HT_Vertical_P8.38mm
Q101: IRF4905PBF; IRF4905_TO220_GSD
R101: 63.4k; R_Axial_DIN0207_L6.3mm_D2.5mm_P10.16mm_Horizontal
R102: 10k; R_Axial_DIN0207_L6.3mm_D2.5mm_P10.16mm_Horizontal
R103: 301k; R_Axial_DIN0207_L6.3mm_D2.5mm_P10.16mm_Horizontal
R104, R106, R108, R113: 100k; R_Axial_DIN0207_L6.3mm_D2.5mm_P10.16mm_Horizontal
R105: 475k; R_Axial_DIN0207_L6.3mm_D2.5mm_P10.16mm_Horizontal
R107: 255k; R_Axial_DIN0207_L6.3mm_D2.5mm_P10.16mm_Horizontal
R109: 68.1k; R_Axial_DIN0207_L6.3mm_D2.5mm_P10.16mm_Horizontal
R111: 600R; R_Axial_DIN0207_L6.3mm_D2.5mm_P10.16mm_Horizontal
R112: 82k; R_Axial_DIN0207_L6.3mm_D2.5mm_P10.16mm_Horizontal
TH101: 10k Semitec 103AT-2; Semitec_103AT2_THT
U1: LM76003RNPT; TI_RNP0030B_LM76003
U2: TPS61088RHLR; TI_RHL0020_TPS61088
U3: LTC4412ES6#TRPBF; TSOT-23-6
U4: AP63205WU-7; SOT-23-6
U5: BQ25171QWDRCRQ1; TI_DRC0010_BQ25171

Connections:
AC1: F101.1, J1.1
AC1F: D1.2 (A), D3.1 (K), F101.2
AC2: D2.2 (A), D4.1 (K), J1.2
BAT: C8.1, C9.1, C10.1, C25.1, C26.1, F102.2, L2.1, R108.1, U2.9 (VIN), U5.10 (OUT)
BATCELL: BT1.1 (+), F102.1, J3.1
BBOOT: C11.1, U2.8 (BOOT)
BCOMP: C15.1, R107.1, U2.18 (COMP)
BCOMP2: C14.1, R107.2
BEN: R108.2, R109.1, U2.2 (EN)
BFB: R105.2, R106.1, U2.17 (FB)
BFSW: R103.1, U2.3 (FSW)
BILIM: R104.1, U2.19 (ILIM)
BOOST_RAW: C16.1, C17.1, C18.1, Q101.3 (D), R105.1, U2.14 (VOUT), U2.15 (VOUT), U2.16 (VOUT), U3.1 (VIN)
BOOT_MAIN: C3.1, U1.6 (BOOT)
BSS: C13.1, U2.10 (SS)
BSW: C11.2, L2.2, U2.4 (SW), U2.5 (SW), U2.6 (SW), U2.7 (SW)
BVCC: C12.1, U2.1 (VCC)
CHBST: C21.1, U4.6 (BST)
CHG5: C22.1, C23.1, C24.1, L3.2, U4.1 (FB), U5.1 (IN)
CHSW: C21.2, L3.1, U4.5 (SW)
GATE: Q101.1 (G), U3.5 (GATE)
GND: BT1.2 (-), C1.2, C2.2, C4.2, C5.2, C6.2, C7.2, C8.2, C9.2, C10.2, C12.2, C13.2, C14.2, C15.2, C16.2, C17.2, C18.2, C19.2, C20.2, C22.2, C23.2, C24.2, C25.2, C26.2, D3.2 (A), D4.2 (A), D105.2 (A2), J2.2, J3.2, R102.2, R103.2, R104.2, R106.2, R109.2, R111.2, R112.2, R113.2, TH101.2, U1.13 (AGND), U1.14 (AGND), U1.15 (AGND), U1.17 (MODE), U1.24 (PGND), U1.25 (PGND), U1.26 (PGND), U1.31 (EP), U2.13 (MODE), U2.20 (AGND), U2.21 (PGND), U3.2 (GND), U3.3 (CTL), U4.4 (GND), U5.3 (CE), U5.5 (GND), U5.11 (EP)
ISET: R111.1, U5.2 (ISET)
MAIN_FB: R101.2, R102.1, U1.12 (FB)
MAIN_RAW: C5.1, C6.1, C7.1, C20.1, D106.2 (A), L1.2, R101.1, U1.9 (BIAS), U4.2 (EN), U4.3 (VIN)
OUT7: C19.1, D106.1 (K), J2.1, Q101.2 (S), U3.6 (SENSE)
SW_MAIN: C3.2, L1.1, U1.1 (SW), U1.2 (SW), U1.3 (SW), U1.4 (SW), U1.5 (SW)
TMR: R113.1, U5.6 (TMR)
TS: TH101.1, U5.4 (TS)
VCC_MAIN: C4.1, U1.8 (VCC)
VRECT: C1.1, C2.1, D1.1 (K), D2.1 (K), D105.1 (A1), U1.18 (EN), U1.20 (PVIN), U1.21 (PVIN), U1.22 (PVIN)
VSET: R112.1, U5.9 (VSET)

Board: 2 copper layers, 59 parts (0 on the bottom side), 32 nets, no tracks yet.
